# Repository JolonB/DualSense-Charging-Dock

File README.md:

# DualSense Charging Dock

In the interest of increased repairability, I've compiled some useful information about the DualSense charging dock.

This includes schematics, pictures, and teardown instructions.

## Teardown

I found the following teardown guides very useful.
Rather than replicating instructions, I'll point you to these resources:

* [Video](https://www.youtube.com/watch?v=xvCFaVB1jn4)
* [Text](https://www.ifixit.com/Answers/View/690457/Dualsense+Charging+Station+Tear+Down+Guide)

Personally, I found the video guide to be more useful.

## Pictures

Images can be found in `assets/images`.

## Schematics

Schematics can be found in the `charging-dock` directory.
These were created using KiCad 8.

The part numbers may not be exact as some of them are based entirely off the two letters written on top.
In most cases, I was unable to get the values of resistors and capacitors, and it is difficult to work out what they should be without knowing the specifications of the other components.
The components with markings are described below:

* WP25141: Current-limited switch. Has enable input to allow power to pass from IN to OUT. Fault detection pin is not connected. I believe this is used for cutting power to the controllers, however, in my simulations, it only works in an undervoltage situation, so won't protect against high-voltage inputs.
* 1AM: [A 3-terminal device, very likely an NPN transistor](https://smd.yooneed.one/code3141.html#code31414d). This is used for enabling the WP25141 switches. When the BJT is open, the output is enabled.
* E2: [Some type of diode, likely a Zener](https://smd.yooneed.one/code4532.html#code4532). I think this is used to only allow the BJT to turn close when the voltage exceeds some threshold. This prevents power reaching the controller in an over-voltage condition.
* GD: [Some type of diode, likely a Zener](https://smd.yooneed.one/code4744.html#code4744). I believe this is used for ESD protection on the input, so it just handles large voltage spikes. I suspect it could be KDZ36B.

Datasheets for the mentioned components can be found in `assets/datasheets`.

The barrel jack footprint is also much bigger than it should be; I just used the closest footprint built in to KiCad.
The charging pin PCB is also not very accurate because I couldn't take it out to measure.

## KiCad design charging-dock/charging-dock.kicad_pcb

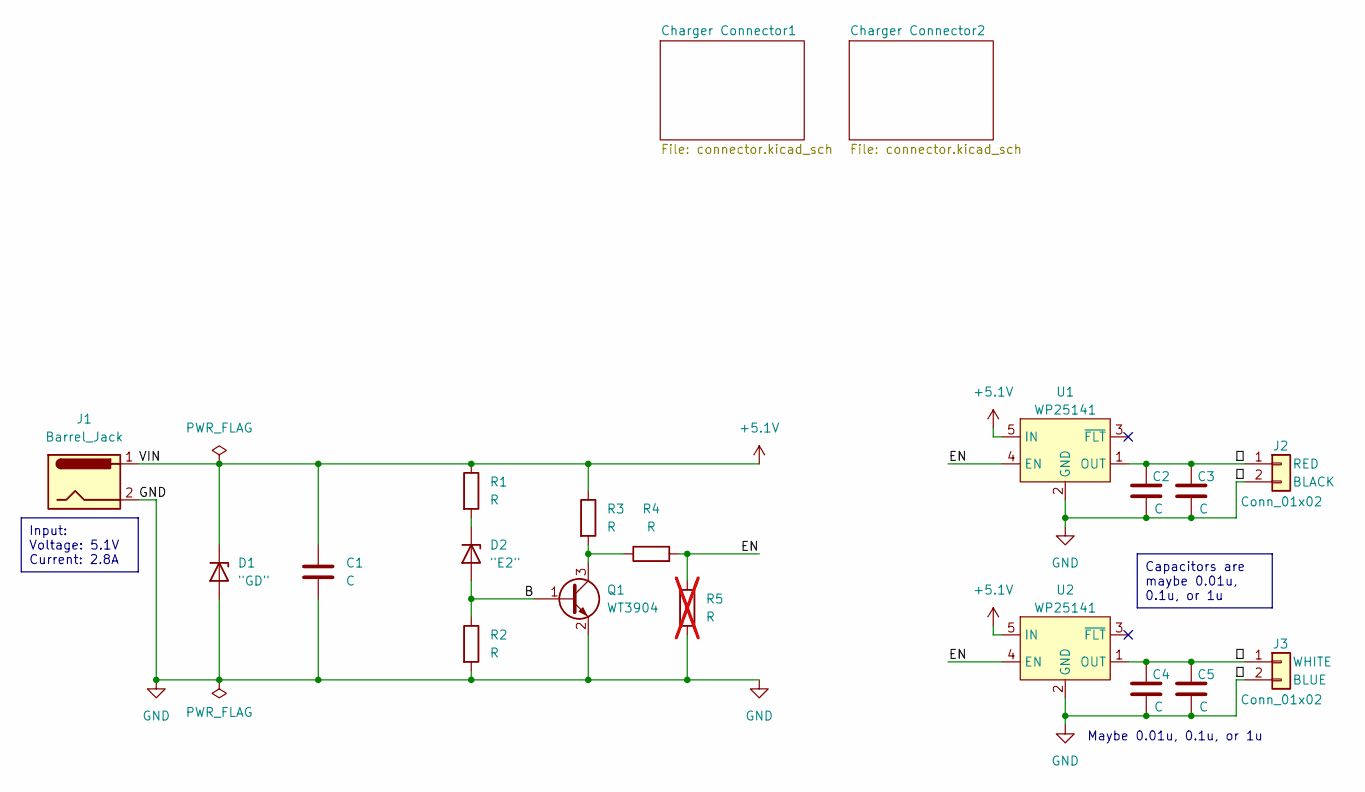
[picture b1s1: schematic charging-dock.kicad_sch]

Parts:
C1, C2, C4: C; C_0603_1608Metric
C3, C5: C; C_0402_1005Metric
D1: "GD"; D_SOD-323F
D2: "E2"; D_SOD-323
J1: Barrel_Jack; BarrelJack_CUI_PJ-079BH_Horizontal
J2, J3: Conn_01x02; Power Pads
Q1: WT3904; SOT-23
R1, R2, R3, R4: R; R_0402_1005Metric
R5: R; R_0402_1005Metric; not fitted
U1, U2: WP25141; SOT-23-5

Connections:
+5.1V: C1.2, D1.1 (K), J1.1, R1.1, R3.1, U1.5 (IN), U2.5 (IN)
/B: D2.2 (A), Q1.1 (B), R2.1
/EN: R4.2, R5.1, U1.4 (EN), U2.4 (EN)
/白: C4.1, C5.1, J3.1, U2.1 (OUT)
/紅: C2.1, C3.1, J2.1, U1.1 (OUT)
GND: C1.1, C2.2, C3.2, C4.2, C5.2, D1.2 (A), J1.2, J1.3, J1.SH, J2.2, J3.2, Q1.2 (E), R2.2, R5.2, U1.2 (GND), U2.2 (GND)
unnamed: D2.1 (K), R1.2
unnamed: Q1.3 (C), R3.2, R4.1

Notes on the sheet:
Capacitors are maybe 0.01u, 0.1u, or 1u
Input: Voltage: 5.1V Current: 2.8A
Maybe 0.01u, 0.1u, or 1u

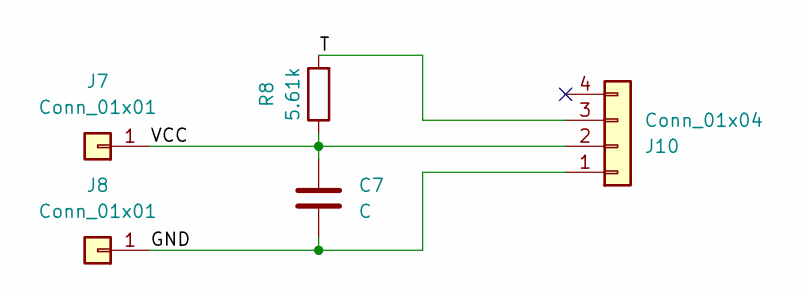
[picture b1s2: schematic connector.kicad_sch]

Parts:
C7: C; C_0402_1005Metric
J7, J8: Conn_01x01; SolderWirePad_1x01_SMD_1x2mm
J10: Conn_01x04; SolderWire-0.1sqmm_1x04_P3.6mm_D0.4mm_OD1mm_Relief
R8: 5.61k; R_0402_1005Metric

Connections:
/Charger Connector1/GND: C7.2, J8.1, J10.1
/Charger Connector1/T: J10.3, R8.2
/Charger Connector1/VCC: C7.1, J7.1, J10.2, R8.1

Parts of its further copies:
C6: C; C_0402_1005Metric
J4, J5: Conn_01x01; SolderWirePad_1x01_SMD_1x2mm
J9: Conn_01x04; SolderWire-0.1sqmm_1x04_P3.6mm_D0.4mm_OD1mm_Relief
R7: 5.61k; R_0402_1005Metric

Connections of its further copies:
/Charger Connector2/GND: C6.2, J5.1, J9.1
/Charger Connector2/T: J9.3, R7.2
/Charger Connector2/VCC: C6.1, J4.1, J9.2, R7.1

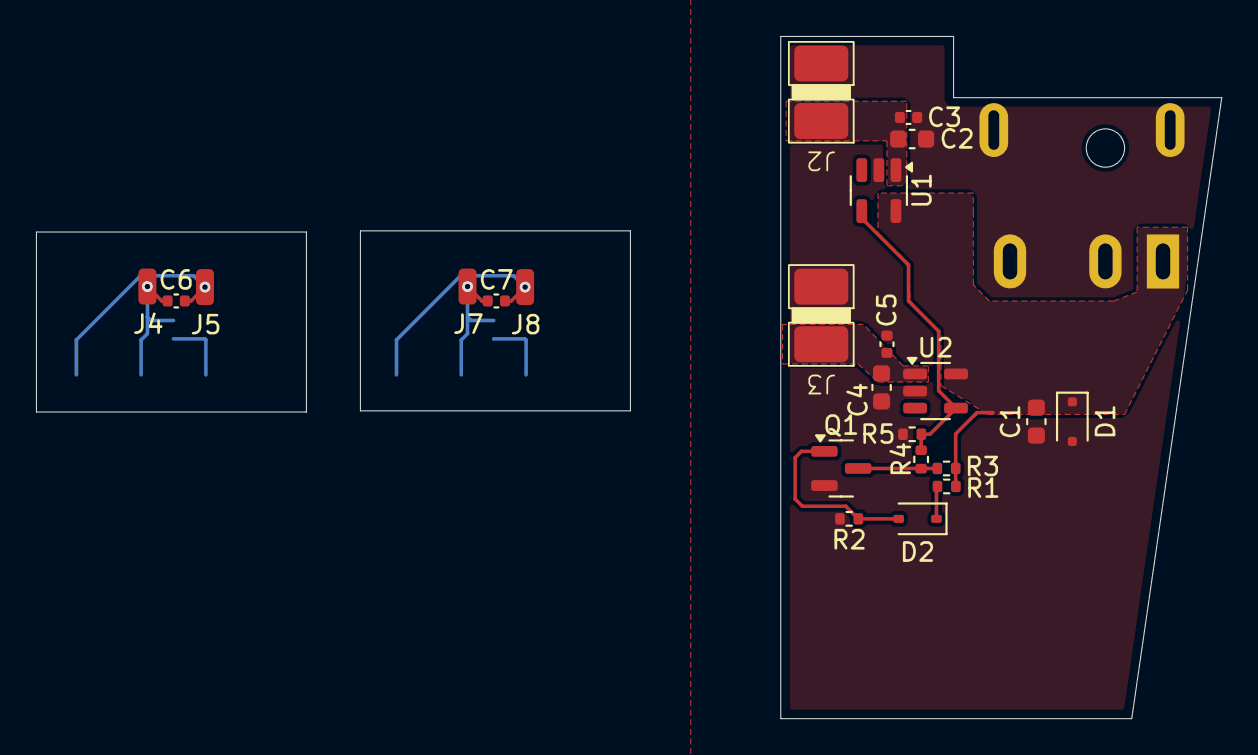
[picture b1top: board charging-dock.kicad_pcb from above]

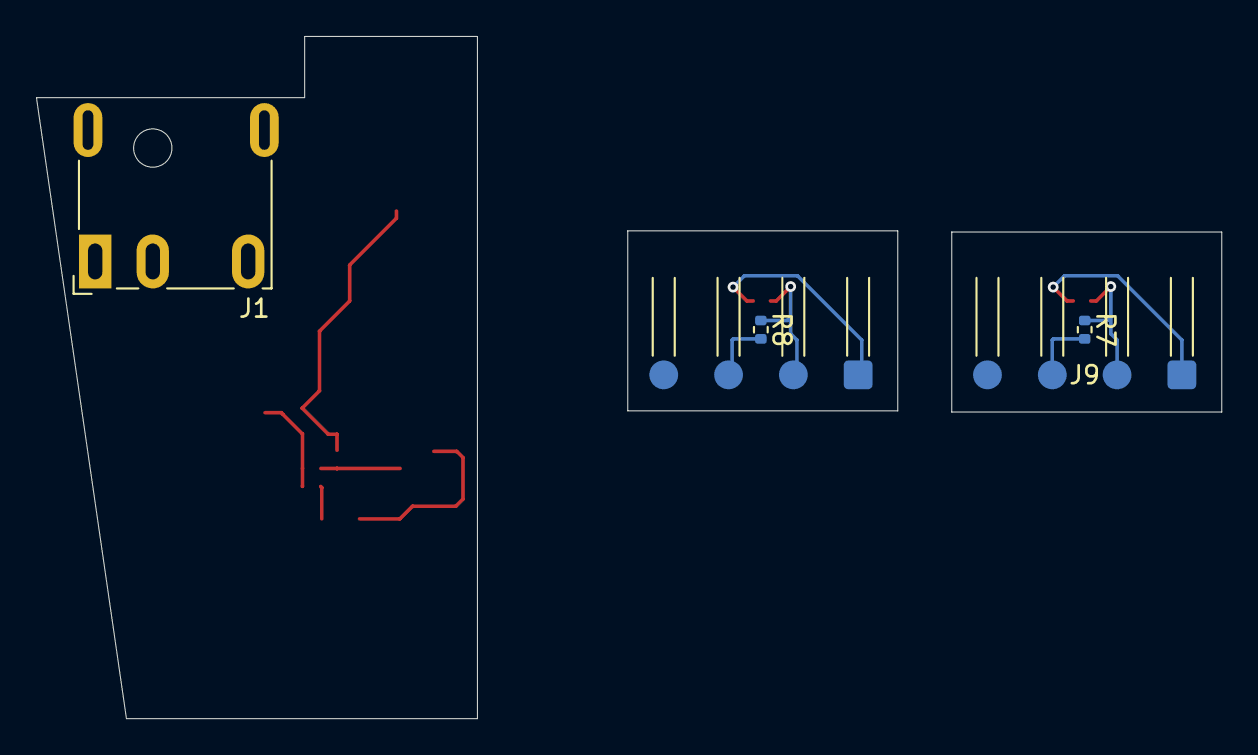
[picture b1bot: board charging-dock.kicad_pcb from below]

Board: 2 copper layers, 65.8 x 37.9 mm, 28 parts (5 on the bottom side), 14 nets.

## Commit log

2024-12-13 Add schematics
2024-12-13 Add images and update README
2024-12-13 Remove LICENSE
    The license was accidentally added. All previous versions should be treated as if no license was present
2024-12-14 Add more information to README
2024-12-14 Update title
